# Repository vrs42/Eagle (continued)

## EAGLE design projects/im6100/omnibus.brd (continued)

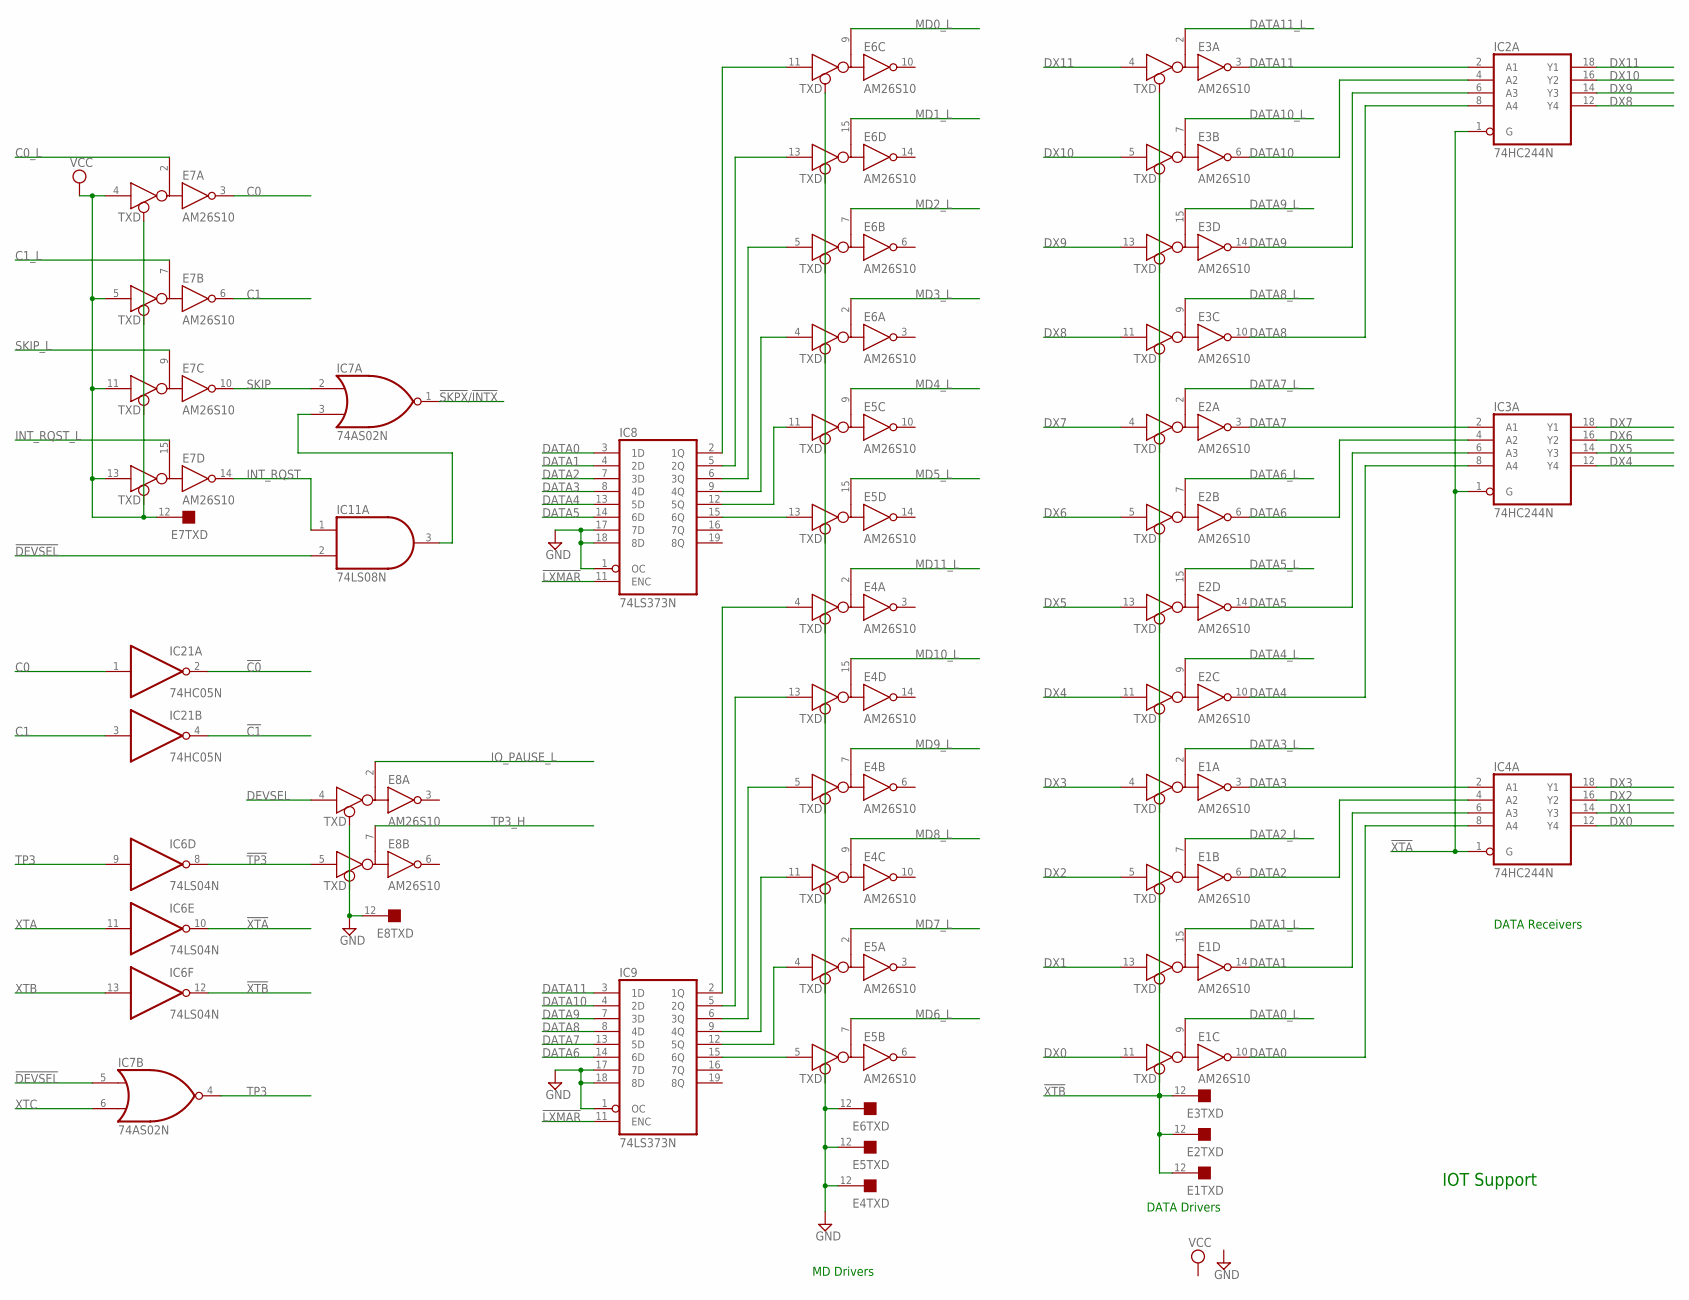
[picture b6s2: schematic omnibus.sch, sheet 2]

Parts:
E1, E2, E3, E4, E5, E6, E7, E8: AM26S10; DIL16
IC2, IC3, IC4: 74HC244N; DIL20
IC6: 74LS04N; DIL14
IC7: 74AS02N; DIL14
IC8, IC9: 74LS373N; DIL20
IC11: 74LS08N; DIL14
IC21: 74HC05N; DIL14

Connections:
!C0: IC21.2 (O); also elsewhere on the board
!C1: IC21.4 (O); also elsewhere on the board
!DEVSEL: IC7.5 (I0), IC11.2 (I1); also elsewhere on the board
!LXMAR: IC8.11 (ENC), IC9.11 (ENC)
!SKPX!/!INTX: IC7.1 (O); also elsewhere on the board
!TP3: E8.5 (D), IC6.8 (O)
!XTA: IC2.1 (G), IC3.1 (G), IC4.1 (G), IC6.10 (O)
!XTB: E1.12 (TXD), E2.12 (TXD), E3.12 (TXD), IC6.12 (O)
C0: E7.3 (R), IC21.1 (I)
C0_L: E7.2 (B); also elsewhere on the board
C1: E7.6 (R), IC21.3 (I)
C1_L: E7.7 (B); also elsewhere on the board
DATA0: E1.10 (R), IC4.8 (A4), IC8.3 (1D)
DATA0_L: E1.9 (B); also elsewhere on the board
DATA1: E1.14 (R), IC4.6 (A3), IC8.4 (2D)
DATA1_L: E1.15 (B); also elsewhere on the board
DATA2: E1.6 (R), IC4.4 (A2), IC8.7 (3D)
DATA2_L: E1.7 (B); also elsewhere on the board
DATA3: E1.3 (R), IC4.2 (A1), IC8.8 (4D)
DATA3_L: E1.2 (B); also elsewhere on the board
DATA4: E2.10 (R), IC3.8 (A4), IC8.13 (5D)
DATA4_L: E2.9 (B); also elsewhere on the board
DATA5: E2.14 (R), IC3.6 (A3), IC8.14 (6D)
DATA5_L: E2.15 (B); also elsewhere on the board
DATA6: E2.6 (R), IC3.4 (A2), IC9.14 (6D)
DATA6_L: E2.7 (B); also elsewhere on the board
DATA7: E2.3 (R), IC3.2 (A1), IC9.13 (5D)
DATA7_L: E2.2 (B); also elsewhere on the board
DATA8: E3.10 (R), IC2.8 (A4), IC9.8 (4D)
DATA8_L: E3.9 (B); also elsewhere on the board
DATA9: E3.14 (R), IC2.6 (A3), IC9.7 (3D)
DATA9_L: E3.15 (B); also elsewhere on the board
DATA10: E3.6 (R), IC2.4 (A2), IC9.4 (2D)
DATA10_L: E3.7 (B); also elsewhere on the board
DATA11: E3.3 (R), IC2.2 (A1), IC9.3 (1D)
DATA11_L: E3.2 (B); also elsewhere on the board
DEVSEL: E8.4 (D); also elsewhere on the board
DX0: E1.11 (D), IC4.12 (Y4); also elsewhere on the board
DX1: E1.13 (D), IC4.14 (Y3); also elsewhere on the board
DX2: E1.5 (D), IC4.16 (Y2); also elsewhere on the board
DX3: E1.4 (D), IC4.18 (Y1); also elsewhere on the board
DX4: E2.11 (D), IC3.12 (Y4); also elsewhere on the board
DX5: E2.13 (D), IC3.14 (Y3); also elsewhere on the board
DX6: E2.5 (D), IC3.16 (Y2); also elsewhere on the board
DX7: E2.4 (D), IC3.18 (Y1); also elsewhere on the board
DX8: E3.11 (D), IC2.12 (Y4); also elsewhere on the board
DX9: E3.13 (D), IC2.14 (Y3); also elsewhere on the board
DX10: E3.5 (D), IC2.16 (Y2); also elsewhere on the board
DX11: E3.4 (D), IC2.18 (Y1); also elsewhere on the board
GND: E1.1 (GND), E1.8 (GND), E2.1 (GND), E2.8 (GND), E3.1 (GND), E3.8 (GND), E4.1 (GND), E4.8 (GND), E4.12 (TXD), E5.1 (GND), E5.8 (GND), E5.12 (TXD), E6.1 (GND), E6.8 (GND), E6.12 (TXD), E7.1 (GND), E7.8 (GND), E8.1 (GND), E8.8 (GND), E8.12 (TXD), IC2.10 (GND), IC3.10 (GND), IC4.10 (GND), IC6.7 (GND), IC7.7 (GND), IC8.1 (OC), IC8.10 (GND), IC8.17 (7D), IC8.18 (8D), IC9.1 (OC), IC9.10 (GND), IC9.17 (7D), IC9.18 (8D), IC11.7 (GND), IC21.7 (GND); also elsewhere on the board
INT_RQST: E7.14 (R), IC11.1 (I0)
INT_RQST_L: E7.15 (B); also elsewhere on the board
IO_PAUSE_L: E8.2 (B); also elsewhere on the board
MD0_L: E6.9 (B); also elsewhere on the board
MD1_L: E6.15 (B); also elsewhere on the board
MD2_L: E6.7 (B); also elsewhere on the board
MD3_L: E6.2 (B); also elsewhere on the board
MD4_L: E5.9 (B); also elsewhere on the board
MD5_L: E5.15 (B); also elsewhere on the board
MD6_L: E5.7 (B); also elsewhere on the board
MD7_L: E5.2 (B); also elsewhere on the board
MD8_L: E4.9 (B); also elsewhere on the board
MD9_L: E4.7 (B); also elsewhere on the board
MD10_L: E4.15 (B); also elsewhere on the board
MD11_L: E4.2 (B); also elsewhere on the board
unnamed: IC7.3 (I1), IC11.3 (O)
unnamed: E6.11 (D), IC8.2 (1Q)
unnamed: E6.13 (D), IC8.5 (2Q)
unnamed: E6.5 (D), IC8.6 (3Q)
unnamed: E6.4 (D), IC8.9 (4Q)
unnamed: E5.11 (D), IC8.12 (5Q)
unnamed: E5.13 (D), IC8.15 (6Q)
unnamed: E5.5 (D), IC9.15 (6Q)
unnamed: E5.4 (D), IC9.12 (5Q)
unnamed: E4.11 (D), IC9.9 (4Q)
unnamed: E4.5 (D), IC9.6 (3Q)
unnamed: E4.13 (D), IC9.5 (2Q)
unnamed: E4.4 (D), IC9.2 (1Q)
SKIP: E7.10 (R), IC7.2 (I0)
SKIP_L: E7.9 (B); also elsewhere on the board
TP3: IC6.9 (I), IC7.4 (O)
TP3_H: E8.7 (B); also elsewhere on the board
VCC: E1.16 (VCC), E2.16 (VCC), E3.16 (VCC), E4.16 (VCC), E5.16 (VCC), E6.16 (VCC), E7.4 (D), E7.5 (D), E7.11 (D), E7.12 (TXD), E7.13 (D), E7.16 (VCC), E8.16 (VCC), IC2.20 (VCC), IC3.20 (VCC), IC4.20 (VCC), IC6.14 (VCC), IC7.14 (VCC), IC8.20 (VCC), IC9.20 (VCC), IC11.14 (VCC), IC21.14 (VCC); also elsewhere on the board
XTA: IC6.11 (I); also elsewhere on the board
XTB: IC6.13 (I); also elsewhere on the board
XTC: IC7.6 (I1); also elsewhere on the board

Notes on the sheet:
DATA Drivers
DATA Receivers
MD Drivers
IOT Support

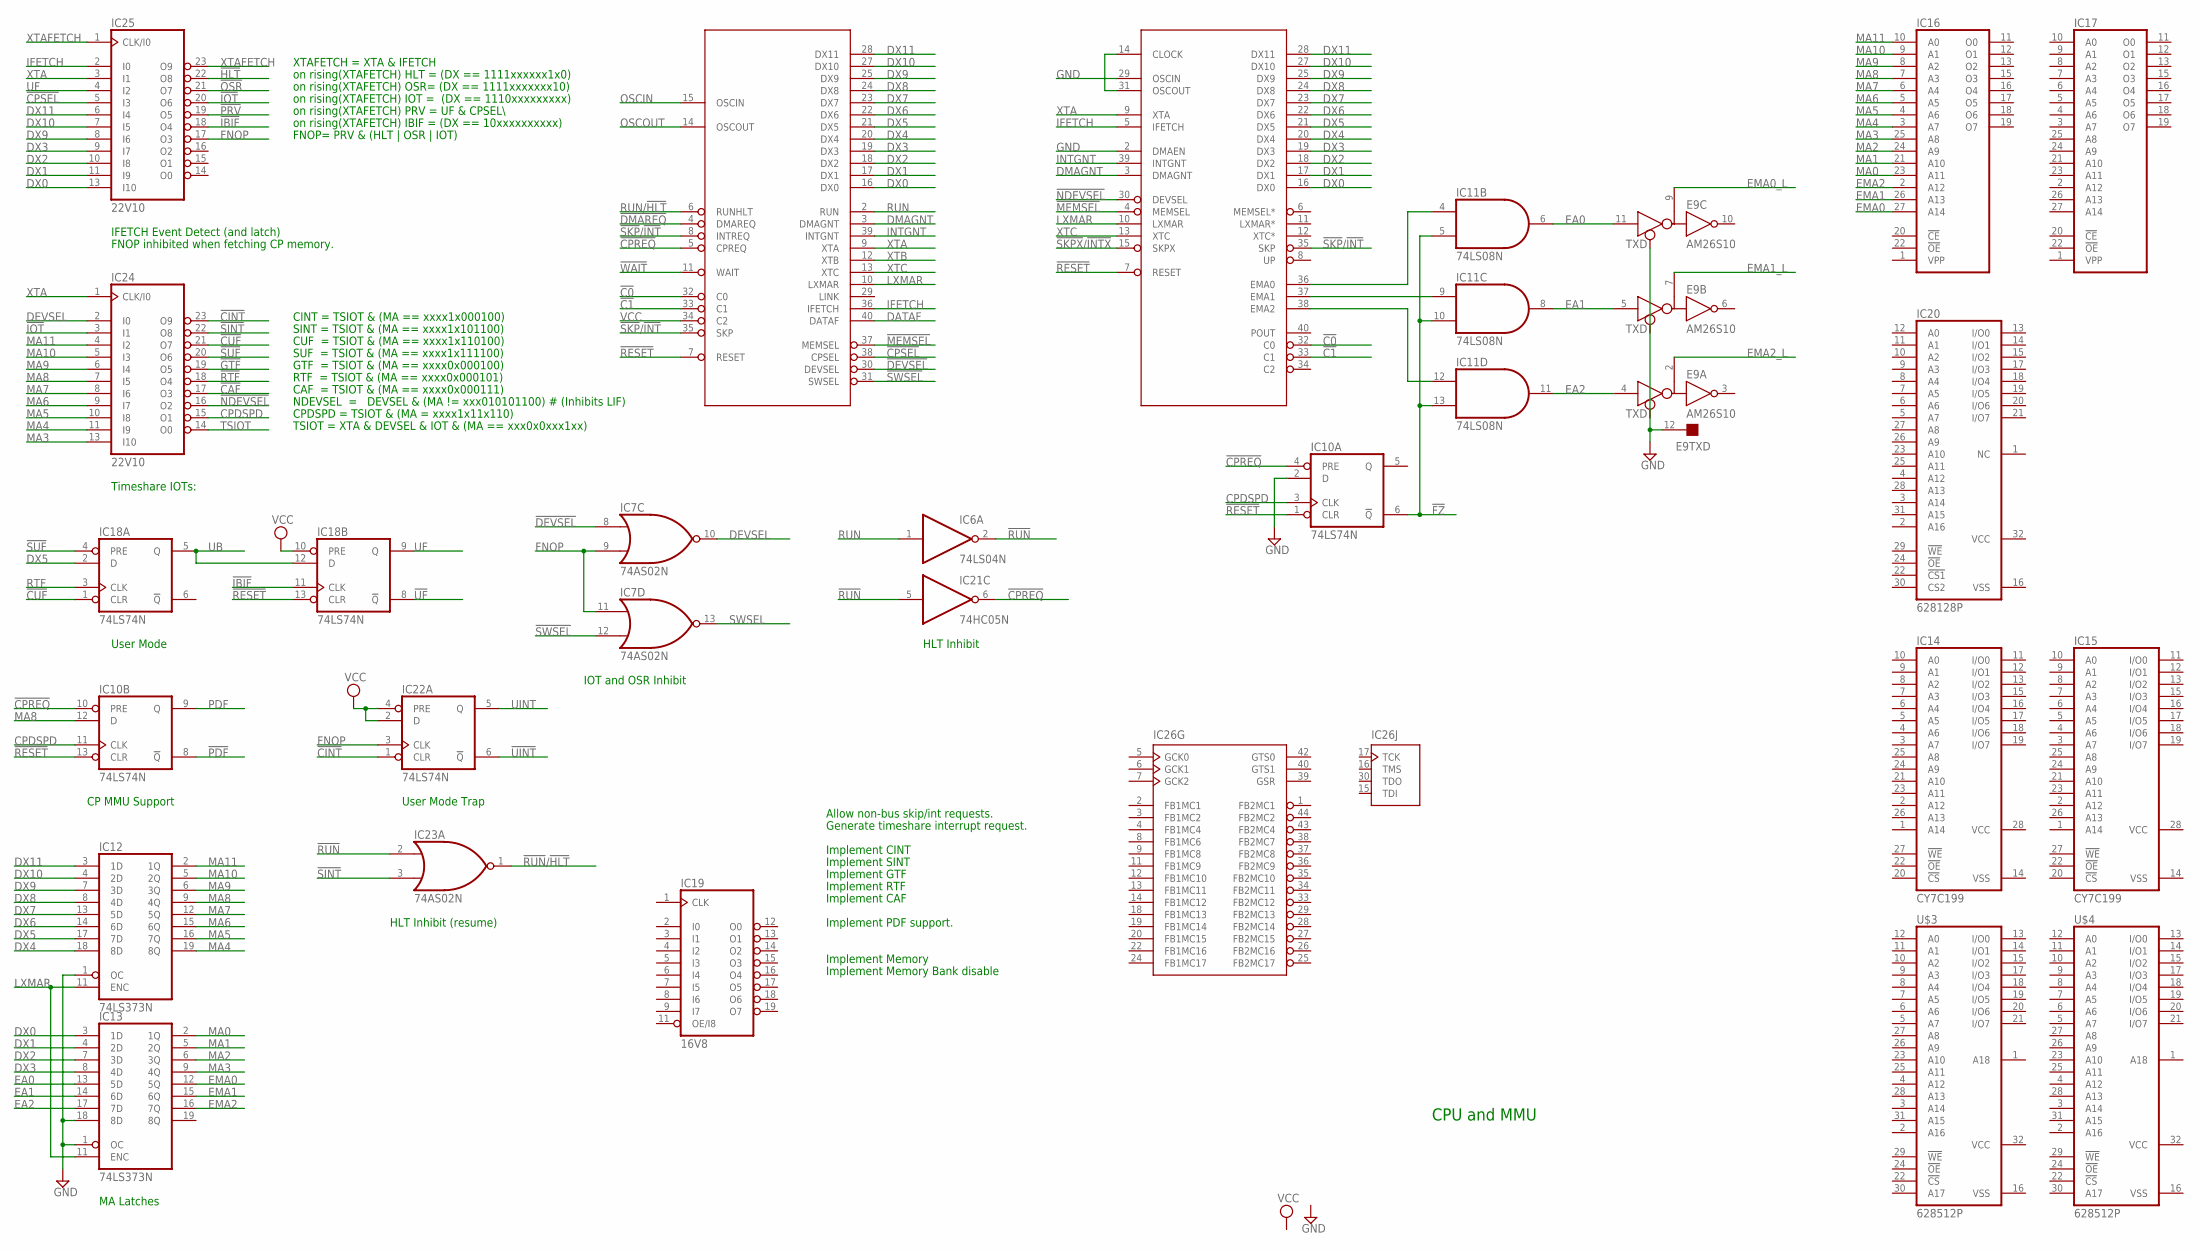
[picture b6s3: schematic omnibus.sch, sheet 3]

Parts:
E9: AM26S10; DIL16
IC1: IM6100; DIL40
IC5: IM6102; DIL40
IC6: 74LS04N; DIL14
IC7, IC23: 74AS02N; DIL14
IC10, IC18, IC22: 74LS74N; DIL14
IC11: 74LS08N; DIL14
IC12, IC13: 74LS373N; DIL20
IC14, IC15: CY7C199; DIL28-3
IC16, IC17: 27256; DIL28
IC19: 16V8; DIL20
IC20: 628128P; DIL32
IC21: 74HC05N; DIL14
IC24, IC25: 22V10; DIL24-3
IC26: XC9536-44; PLCC-S44
U$3, U$4: 628512P; DIL32

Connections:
!C0: IC1.32 (C0), IC5.32 (C0); also elsewhere on the board
!C1: IC1.33 (C1), IC5.33 (C1); also elsewhere on the board
!CAF: IC24.17 (O3)
!CINT: IC22.1 (CLR), IC24.23 (O9)
!CPREQ: IC1.5 (CPREQ), IC10.4 (PRE), IC10.10 (PRE), IC21.6 (O)
!CPSEL: IC1.38 (CPSEL), IC25.5 (I3)
!CUF: IC18.1 (CLR), IC24.21 (O7)
!DEVSEL: IC1.30 (DEVSEL), IC7.8 (I0); also elsewhere on the board
!DMAREQ: IC1.4 (DMAREQ)
!FZ: IC10.6 (!Q), IC11.5 (I1), IC11.10 (I1), IC11.13 (I1)
!GTF: IC24.19 (O5)
!HLT: IC25.22 (O8)
!IBIF: IC18.11 (CLK), IC25.18 (O4)
!IOT: IC24.3 (I1), IC25.20 (O6)
!MEMSEL: IC1.37 (MEMSEL), IC5.4 (MEMSEL)
!NDEVSEL: IC5.30 (DEVSEL), IC24.16 (O2)
!OSR: IC25.21 (O7)
!PDF: IC10.8 (!Q)
!PRV: IC25.19 (O5)
!RESET: IC1.7 (RESET), IC5.7 (RESET), IC10.1 (CLR), IC10.13 (CLR), IC18.13 (CLR)
!RTF: IC24.18 (O4)
!RUN: IC6.2 (O), IC21.5 (I), IC23.2 (I0)
!RUN!/!HLT: IC23.1 (O)
!SINT: IC23.3 (I1), IC24.22 (O8)
!SKP!/!INT: IC1.8 (INTREQ), IC1.35 (SKP), IC5.35 (SKP)
!SKPX!/!INTX: IC5.15 (SKPX); also elsewhere on the board
!SUF: IC18.4 (PRE), IC24.20 (O6)
!SWSEL: IC1.31 (SWSEL), IC7.12 (I1)
!UF: IC18.8 (!Q)
!UINT: IC22.6 (!Q)
!WAIT: IC1.11 (WAIT)
CPDSPD: IC10.3 (CLK), IC10.11 (CLK), IC24.15 (O1)
DATAF: IC1.40 (DATAF)
DEVSEL: IC7.10 (O), IC24.2 (I0); also elsewhere on the board
DMAGNT: IC1.3 (DMAGNT), IC5.3 (DMAGNT)
DX0: IC1.16 (DX0), IC5.16 (DX0), IC13.3 (1D), IC25.13 (I10); also elsewhere on the board
DX1: IC1.17 (DX1), IC5.17 (DX1), IC13.4 (2D), IC25.11 (I9); also elsewhere on the board
DX2: IC1.18 (DX2), IC5.18 (DX2), IC13.7 (3D), IC25.10 (I8); also elsewhere on the board
DX3: IC1.19 (DX3), IC5.19 (DX3), IC13.8 (4D), IC25.9 (I7); also elsewhere on the board
DX4: IC1.20 (DX4), IC5.20 (DX4), IC12.18 (8D); also elsewhere on the board
DX5: IC1.21 (DX5), IC5.21 (DX5), IC12.17 (7D), IC18.2 (D); also elsewhere on the board
DX6: IC1.22 (DX6), IC5.22 (DX6), IC12.14 (6D); also elsewhere on the board
DX7: IC1.23 (DX7), IC5.23 (DX7), IC12.13 (5D); also elsewhere on the board
DX8: IC1.24 (DX8), IC5.24 (DX8), IC12.8 (4D); also elsewhere on the board
DX9: IC1.25 (DX9), IC5.25 (DX9), IC12.7 (3D), IC25.8 (I6); also elsewhere on the board
DX10: IC1.27 (DX10), IC5.27 (DX10), IC12.4 (2D), IC25.7 (I5); also elsewhere on the board
DX11: IC1.28 (DX11), IC5.28 (DX11), IC12.3 (1D), IC25.6 (I4); also elsewhere on the board
EA0: E9.11 (D), IC11.6 (O), IC13.13 (5D)
EA1: E9.5 (D), IC11.8 (O), IC13.14 (6D)
EA2: E9.4 (D), IC11.11 (O), IC13.17 (7D)
EMA0: IC13.12 (5Q), IC16.27 (A14)
EMA0_L: E9.9 (B); also elsewhere on the board
EMA1: IC13.15 (6Q), IC16.26 (A13)
EMA1_L: E9.7 (B); also elsewhere on the board
EMA2: IC13.16 (7Q), IC16.2 (A12)
EMA2_L: E9.2 (B); also elsewhere on the board
FNOP: IC7.9 (I1), IC7.11 (I0), IC22.3 (CLK), IC25.17 (O3)
GND: E9.1 (GND), E9.8 (GND), E9.12 (TXD), IC1.26 (GND), IC5.2 (DMAEN), IC5.26 (GND), IC5.29 (OSCIN), IC6.7 (GND), IC7.7 (GND), IC10.2 (D), IC10.7 (GND), IC11.7 (GND), IC12.1 (OC), IC12.10 (GND), IC13.1 (OC), IC13.10 (GND), IC13.18 (8D), IC16.14 (GND), IC17.14 (GND), IC18.7 (GND), IC19.10 (GND), IC21.7 (GND), IC22.7 (GND), IC23.7 (GND), IC24.12 (GND), IC25.12 (GND), IC26.10 (GND), IC26.23 (GND), IC26.31 (GND); also elsewhere on the board
IFETCH: IC1.36 (IFETCH), IC5.5 (IFETCH), IC25.2 (I0)
INTGNT: IC1.39 (INTGNT), IC5.39 (INTGNT)
LXMAR: IC1.10 (LXMAR), IC5.10 (LXMAR), IC12.11 (ENC), IC13.11 (ENC)
MA0: IC13.2 (1Q), IC16.23 (A11)
MA1: IC13.5 (2Q), IC16.21 (A10)
MA2: IC13.6 (3Q), IC16.24 (A9)
MA3: IC13.9 (4Q), IC16.25 (A8), IC24.13 (I10)
MA4: IC12.19 (8Q), IC16.3 (A7), IC24.11 (I9)
MA5: IC12.16 (7Q), IC16.4 (A6), IC24.10 (I8)
MA6: IC12.15 (6Q), IC16.5 (A5), IC24.9 (I7)
MA7: IC12.12 (5Q), IC16.6 (A4), IC24.8 (I6)
MA8: IC10.12 (D), IC12.9 (4Q), IC16.7 (A3), IC24.7 (I5)
MA9: IC12.6 (3Q), IC16.8 (A2), IC24.6 (I4)
MA10: IC12.5 (2Q), IC16.9 (A1), IC24.5 (I3)
MA11: IC12.2 (1Q), IC16.10 (A0), IC24.4 (I2)
unnamed: IC5.14 (CLOCK), IC5.31 (OSCOUT)
unnamed: IC5.37 (EMA1), IC11.9 (I0)
unnamed: IC5.36 (EMA0), IC11.4 (I0)
unnamed: IC5.38 (EMA2), IC11.12 (I0)
OSCIN: IC1.15 (OSCIN)
OSCOUT: IC1.14 (OSCOUT)
PDF: IC10.9 (Q)
RTF: IC18.3 (CLK)
RUN: IC1.2 (RUN), IC6.1 (I)
RUN/!HLT: IC1.6 (RUNHLT)
SWSEL: IC7.13 (O)
TSIOT: IC24.14 (O0)
UB: IC18.5 (Q), IC18.12 (D)
UF: IC18.9 (Q), IC25.4 (I2)
UINT: IC22.5 (Q)
VCC: E9.16 (VCC), IC1.1 (VCC), IC1.34 (C2), IC5.1 (VCC), IC6.14 (VCC), IC7.14 (VCC), IC10.14 (VCC), IC11.14 (VCC), IC12.20 (VCC), IC13.20 (VCC), IC14.28 (VCC), IC15.28 (VCC), IC16.28 (VCC), IC17.28 (VCC), IC18.10 (PRE), IC18.14 (VCC), IC19.20 (VCC), IC20.32 (VCC), IC21.14 (VCC), IC22.2 (D), IC22.4 (PRE), IC22.14 (VCC), IC23.14 (VCC), IC24.24 (VCC), IC25.24 (VCC), IC26.21 (VCC), IC26.32 (VCC), IC26.41 (VCC), U$3.32 (VCC), U$4.32 (VCC); also elsewhere on the board
VSS: IC14.14 (VSS), IC15.14 (VSS), IC20.16 (VSS), U$3.16 (VSS), U$4.16 (VSS)
XTA: IC1.9 (XTA), IC5.9 (XTA), IC24.1 (CLK/I0), IC25.3 (I1); also elsewhere on the board
XTAFETCH: IC25.1 (CLK/I0), IC25.23 (O9)
XTB: IC1.12 (XTB); also elsewhere on the board
XTC: IC1.13 (XTC), IC5.13 (XTC); also elsewhere on the board

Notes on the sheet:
CPU and MMU
Timeshare IOTs:
CINT = TSIOT & (MA == xxxx1x000100)
SINT = TSIOT & (MA == xxxx1x101100)
CUF = TSIOT & (MA == xxxx1x110100)
SUF = TSIOT & (MA == xxxx1x111100)
GTF = TSIOT & (MA == xxxx0x000100)
RTF = TSIOT & (MA == xxxx0x000101)
CAF = TSIOT & (MA == xxxx0x000111)
NDEVSEL = DEVSEL & (MA \!= xxx010101100) # (Inhibits LIF)
CPDSPD = TSIOT & (MA = xxxx1x11x110)
IFETCH Event Detect (and latch)
on rising(XTAFETCH) HLT = (DX == 1111xxxxxx1x0)
on rising(XTAFETCH) OSR= (DX == 1111xxxxxxx10)
on rising(XTAFETCH) IOT = (DX == 1110xxxxxxxxx)
FNOP= PRV & (HLT | OSR | IOT)
on rising(XTAFETCH) IBIF = (DX == 10xxxxxxxxxx)
XTAFETCH = XTA & IFETCH
TSIOT = XTA & DEVSEL & IOT & (MA == xxx0x0xxx1xx)
on rising(XTAFETCH) PRV = UF & CPSEL\\
FNOP inhibited when fetching CP memory.
MA Latches
User Mode
CP MMU Support
IOT and OSR Inhibit
HLT Inhibit
Generate timeshare interrupt request.
Allow non-bus skip/int requests.
Implement CINT
Implement SINT
Implement GTF
Implement RTF
Implement CAF
Implement Memory
Implement Memory Bank disable
Implement PDF support.
HLT Inhibit (resume)
User Mode Trap

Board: 2 copper layers, 39 parts (0 on the bottom side), 138 nets, no tracks yet.

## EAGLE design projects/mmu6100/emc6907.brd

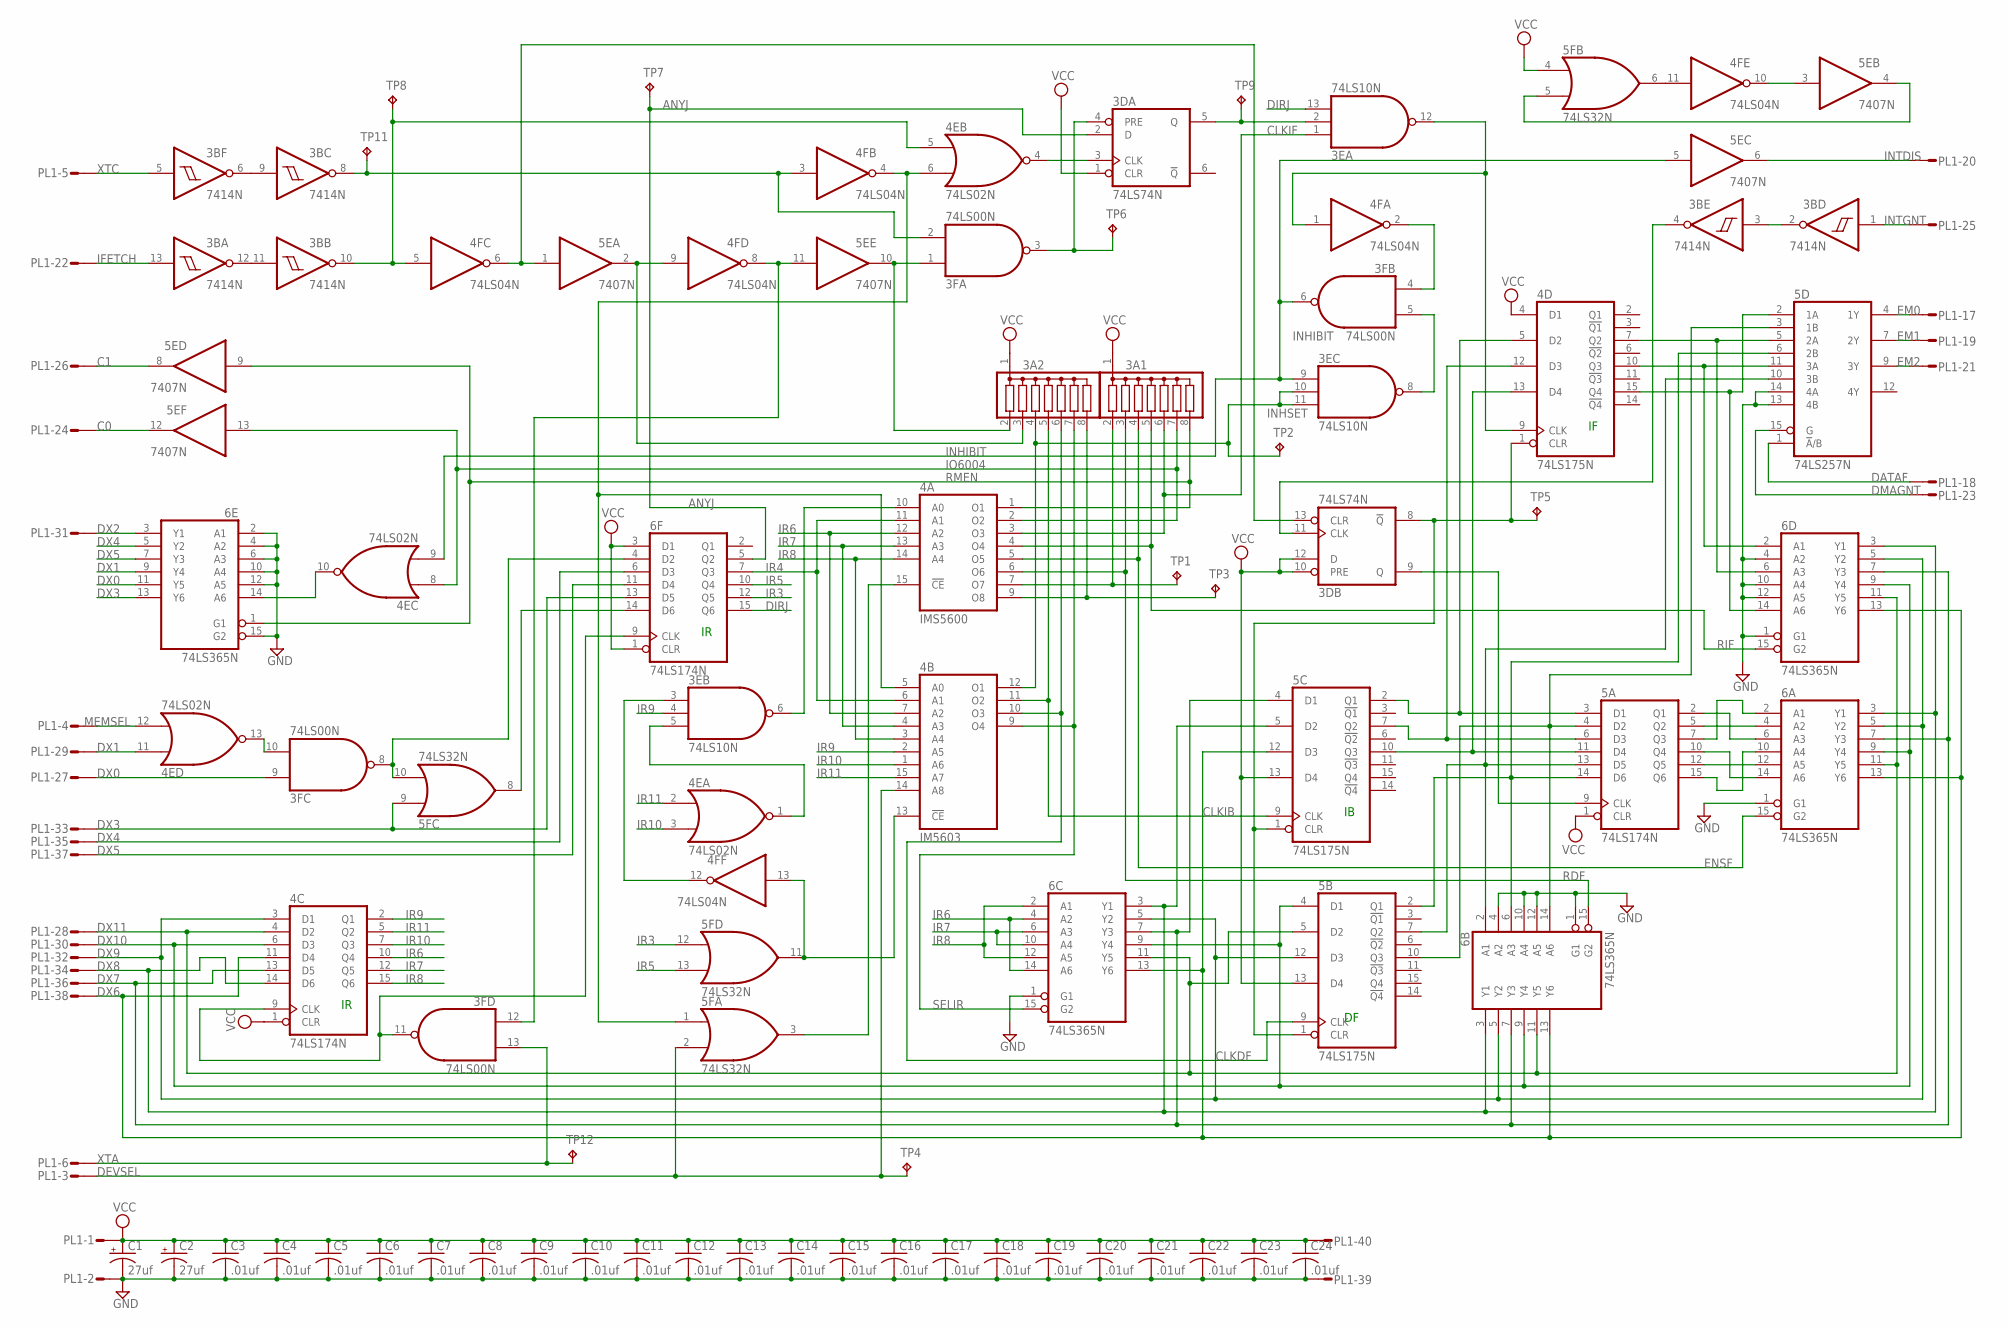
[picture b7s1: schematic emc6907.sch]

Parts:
3A1, 3A2: G07R; SIL8
3B: 7414N; DIL14
3D: 74LS74N; DIL14
3E: 74LS10N; DIL14
3F: 74LS00N; DIL14
4A: IMS5600; DIL16
4B: IM5603; DIL16
4C, 5A, 6F: 74LS174N; DIL16
4D, 5B, 5C: 74LS175N; DIL16
4E: 74LS02N; DIL14
4F: 74LS04N; DIL14
5D: 74LS257N; DIL16
5E: 7407N; DIL14
5F: 74LS32N; DIL14
6A, 6B, 6C, 6D, 6E: 74LS365N; DIL16
C1, C2: 27uf; E22-6
C3, C4, C5, C6, C7, C8, C9, C10, C11, C12, C13, C14, C15, C16, C17, C18, C19, C20, C21, C22, C23, C24: .01uf; C050-025X075
PL1: 40VS; 40V
TP1, TP2, TP3, TP4, TP5, TP6, TP7, TP8, TP9, TP11, TP12: TPPAD1-13; P1-13

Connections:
ANYJ: 3D.2 (D), 6F.5 (Q2), TP7.TP
C0: 5E.12 (O), PL1.24
C1: 5E.8 (O), PL1.26
CLKDF: 3A2.6, 4B.10 (O3), 5B.9 (CLK)
CLKIB: 3A2.5, 4B.11 (O2), 5C.9 (CLK)
CLKIF: 3A1.6, 3E.1 (I0), 4A.3 (O3)
DATAF: 5D.1 (!A!/B), PL1.18
DEVSEL: 4B.14 (A8), 5F.2 (I1), PL1.3, TP4.TP
DIRJ: 3E.13 (I2), 6F.15 (Q6)
DMAGNT: 5D.15 (G), PL1.23
DX0: 3F.9 (I0), 6E.11 (Y5), PL1.27
DX1: 4E.11 (I0), 6E.9 (Y4), PL1.29
DX2: 6E.3 (Y1), PL1.31
DX3: 5F.9 (I0), 6E.13 (Y6), 6F.13 (D5), PL1.33
DX4: 6E.5 (Y2), 6F.6 (D3), PL1.35
DX5: 6E.7 (Y3), 6F.11 (D4), PL1.37
DX6: 4C.11 (D4), 5C.12 (D3), 6A.13 (Y6), 6B.13 (Y6), 6C.13 (Y6), 6D.13 (Y6), PL1.38
DX7: 4C.13 (D5), 5C.4 (D1), 6A.7 (Y3), 6B.7 (Y3), 6C.7 (Y3), 6D.7 (Y3), PL1.36
DX8: 4C.14 (D6), 5C.5 (D2), 6A.3 (Y1), 6B.3 (Y1), 6C.3 (Y1), 6D.3 (Y1), PL1.34
DX9: 4C.3 (D1), 5B.12 (D3), 6A.5 (Y2), 6B.5 (Y2), 6C.5 (Y2), 6D.5 (Y2), PL1.32
DX10: 4C.6 (D3), 5B.4 (D1), 6A.9 (Y4), 6B.9 (Y4), 6C.9 (Y4), 6D.9 (Y4), PL1.30
DX11: 4C.4 (D2), 5B.5 (D2), 6A.11 (Y5), 6B.11 (Y5), 6C.11 (Y5), 6D.11 (Y5), PL1.28
EM0: 5D.4 (1Y), PL1.17
EM1: 5D.7 (2Y), PL1.19
EM2: 5D.9 (3Y), PL1.21
ENSF: 3A1.4, 4A.5 (O5), 6A.15 (G2)
GND: 3B.7 (GND), 3D.7 (GND), 3E.7 (GND), 3F.7 (GND), 4A.8 (GND), 4B.8 (GND), 4C.8 (GND), 4D.8 (GND), 4E.7 (GND), 4F.7 (GND), 5A.8 (GND), 5B.8 (GND), 5C.8 (GND), 5D.8 (GND), 5D.13 (4B), 5D.14 (4A), 5E.7 (GND), 5F.7 (GND), 6A.1 (G1), 6A.8 (GND), 6B.1 (G1), 6B.4 (A2), 6B.8 (GND), 6B.10 (A4), 6B.12 (A5), 6C.1 (G1), 6C.8 (GND), 6D.1 (G1), 6D.4 (A2), 6D.8 (GND), 6D.10 (A4), 6D.12 (A5), 6E.2 (A1), 6E.4 (A2), 6E.6 (A3), 6E.8 (GND), 6E.10 (A4), 6E.12 (A5), 6E.15 (G2), 6F.8 (GND), C1.-, C2.-, C3.2, C4.2, C5.2, C6.2, C7.2, C8.2, C9.2, C10.2, C11.2, C12.2, C13.2, C14.2, C15.2, C16.2, C17.2, C18.2, C19.2, C20.2, C21.2, C22.2, C23.2, C24.2, PL1.2, PL1.39
IFETCH: 3B.13 (I), PL1.22
INHIBIT: 3E.9 (I0), 3F.6 (O), 4E.9 (I1), 5E.5 (I)
INHSET: 3A2.4, 3E.10 (I1), 3E.11 (I2), 4B.12 (O1), TP2.TP
INTDIS: 5E.6 (O), PL1.20
INTGNT: 3B.1 (I), PL1.25
IO6004: 3A1.7, 4A.2 (O2), 4E.8 (I0), 5E.13 (I)
IR3: 5F.12 (I0), 6F.12 (Q5)
IR4: 4A.11 (A1), 4B.6 (A1), 6F.7 (Q3)
IR5: 5F.13 (I1), 6F.10 (Q4)
IR6: 4A.12 (A2), 4B.7 (A2), 4C.10 (Q4), 6C.4 (A2), 6C.14 (A6)
IR7: 4A.13 (A3), 4B.4 (A3), 4C.12 (Q5), 6C.6 (A3), 6C.10 (A4)
IR8: 4A.14 (A4), 4B.3 (A4), 4C.15 (Q6), 6C.2 (A1), 6C.12 (A5)
IR9: 3E.4 (I1), 4B.2 (A5), 4C.2 (Q1)
IR10: 4B.1 (A6), 4C.7 (Q3), 4E.3 (I1)
IR11: 4B.15 (A7), 4C.5 (Q2), 4E.2 (I0)
LOADIR: 3F.11 (O), 4C.9 (CLK), 6F.9 (CLK)
MEMSEL: 4E.12 (I1), PL1.4
unnamed: 3B.11 (I), 3B.12 (O)
unnamed: 3B.6 (O), 3B.9 (I)
unnamed: 3B.8 (O), 3F.2 (I1), 4F.3 (I), TP11.TP
unnamed: 3B.10 (O), 4E.5 (I0), 4F.5 (I), TP8.TP
unnamed: 3D.13 (CLR), 4F.6 (O), 5E.1 (I)
unnamed: 3D.5 (Q), 3E.2 (I1), TP9.TP
unnamed: 3A2.2, 3F.1 (I0), 5E.10 (O)
unnamed: 3F.12 (I0), 4F.8 (O), 5E.11 (I)
unnamed: 3A2.3, 4F.9 (I), 5E.2 (O)
unnamed: 4B.5 (A0), 4E.6 (I1), 4F.4 (O), 5F.1 (I0)
unnamed: 3D.3 (CLK), 4E.4 (O)
unnamed: 3D.4 (PRE), 3F.3 (O), TP6.TP
unnamed: 4F.11 (I), 5F.6 (O)
unnamed: 3F.10 (I1), 4E.13 (O)
unnamed: 4E.10 (O), 6E.14 (A6)
unnamed: 5E.4 (O), 5F.5 (I1)
unnamed: 4F.10 (O), 5E.3 (I)
unnamed: 3F.8 (O), 5F.10 (I1), 6F.4 (D2)
unnamed: 5F.8 (O), 6F.14 (D6)
unnamed: 4B.13 (!CE), 4F.13 (I), 5F.11 (O)
unnamed: 3A1.2, 4A.7 (O7), TP1.TP
unnamed: 3A2.8, 4A.9 (O8), TP3.TP
unnamed: 3E.3 (I0), 4F.12 (O)
unnamed: 3E.6 (O), 4A.10 (A0)
unnamed: 4A.15 (!CE), 5F.3 (O)
unnamed: 5A.2 (Q1), 6A.6 (A3)
unnamed: 3E.5 (I2), 4E.1 (O)
unnamed: 5A.10 (Q4), 6A.14 (A6)
unnamed: 5A.7 (Q3), 6A.2 (A1)
unnamed: 5A.5 (Q2), 6A.4 (A2)
unnamed: 5A.15 (Q6), 6A.10 (A4)
unnamed: 5A.12 (Q5), 6A.12 (A5)
unnamed: 4D.15 (Q4), 5D.2 (1A), 6D.14 (A6)
unnamed: 4D.10 (Q3), 5D.11 (3A), 6D.2 (A1)
unnamed: 4D.7 (Q2), 5D.5 (2A), 6D.6 (A3)
unnamed: 3D.8 (!Q), 4D.1 (CLR), 5B.1 (CLR), 5C.1 (CLR), TP5.TP
unnamed: 4D.13 (D4), 5A.11 (D4), 5C.10 (Q3)
unnamed: 4D.5 (D2), 5A.3 (D1), 5C.2 (Q1)
unnamed: 4D.12 (D3), 5A.6 (D3), 5C.7 (Q2)
unnamed: 5A.4 (D2), 5B.10 (Q3), 5D.3 (1B), 6B.14 (A6)
unnamed: 5A.14 (D6), 5B.2 (Q1), 5D.6 (2B), 6B.6 (A3)
unnamed: 5A.13 (D5), 5B.7 (Q2), 5D.10 (3B), 6B.2 (A1)
unnamed: 3D.9 (Q), 5A.9 (CLK)
unnamed: 3E.12 (O), 4D.9 (CLK), 4F.1 (I)
unnamed: 3E.8 (O), 3F.5 (I1)
unnamed: 3F.4 (I0), 4F.2 (O)
unnamed: 3B.2 (O), 3B.3 (I)
unnamed: 3B.4 (O), 3D.11 (CLK)
RDF: 3A1.3, 4A.6 (O6), 6B.15 (G2)
RIF: 3A1.5, 4A.4 (O4), 6D.15 (G2)
RMEN: 3A1.8, 4A.1 (O1), 5E.9 (I), 6E.1 (G1)
SELIR: 3A2.7, 4B.9 (O4), 6C.15 (G2)
VCC: 3A1.1, 3A2.1, 3B.14 (VCC), 3D.1 (CLR), 3D.10 (PRE), 3D.12 (D), 3D.14 (VCC), 3E.14 (VCC), 3F.14 (VCC), 4A.16 (VCC), 4B.16 (VCC), 4C.1 (CLR), 4C.16 (VCC), 4D.4 (D1), 4D.16 (VCC), 4E.14 (VCC), 4F.14 (VCC), 5A.1 (CLR), 5A.16 (VCC), 5B.13 (D4), 5B.16 (VCC), 5C.13 (D4), 5C.16 (VCC), 5D.16 (VCC), 5E.14 (VCC), 5F.4 (I0), 5F.14 (VCC), 6A.16 (VCC), 6B.16 (VCC), 6C.16 (VCC), 6D.16 (VCC), 6E.16 (VCC), 6F.1 (CLR), 6F.3 (D1), 6F.16 (VCC), C1.+, C2.+, C3.1, C4.1, C5.1, C6.1, C7.1, C8.1, C9.1, C10.1, C11.1, C12.1, C13.1, C14.1, C15.1, C16.1, C17.1, C18.1, C19.1, C20.1, C21.1, C22.1, C23.1, C24.1, PL1.1, PL1.40
XTA: 3F.13 (I1), PL1.6, TP12.TP
XTC: 3B.5 (I), PL1.5

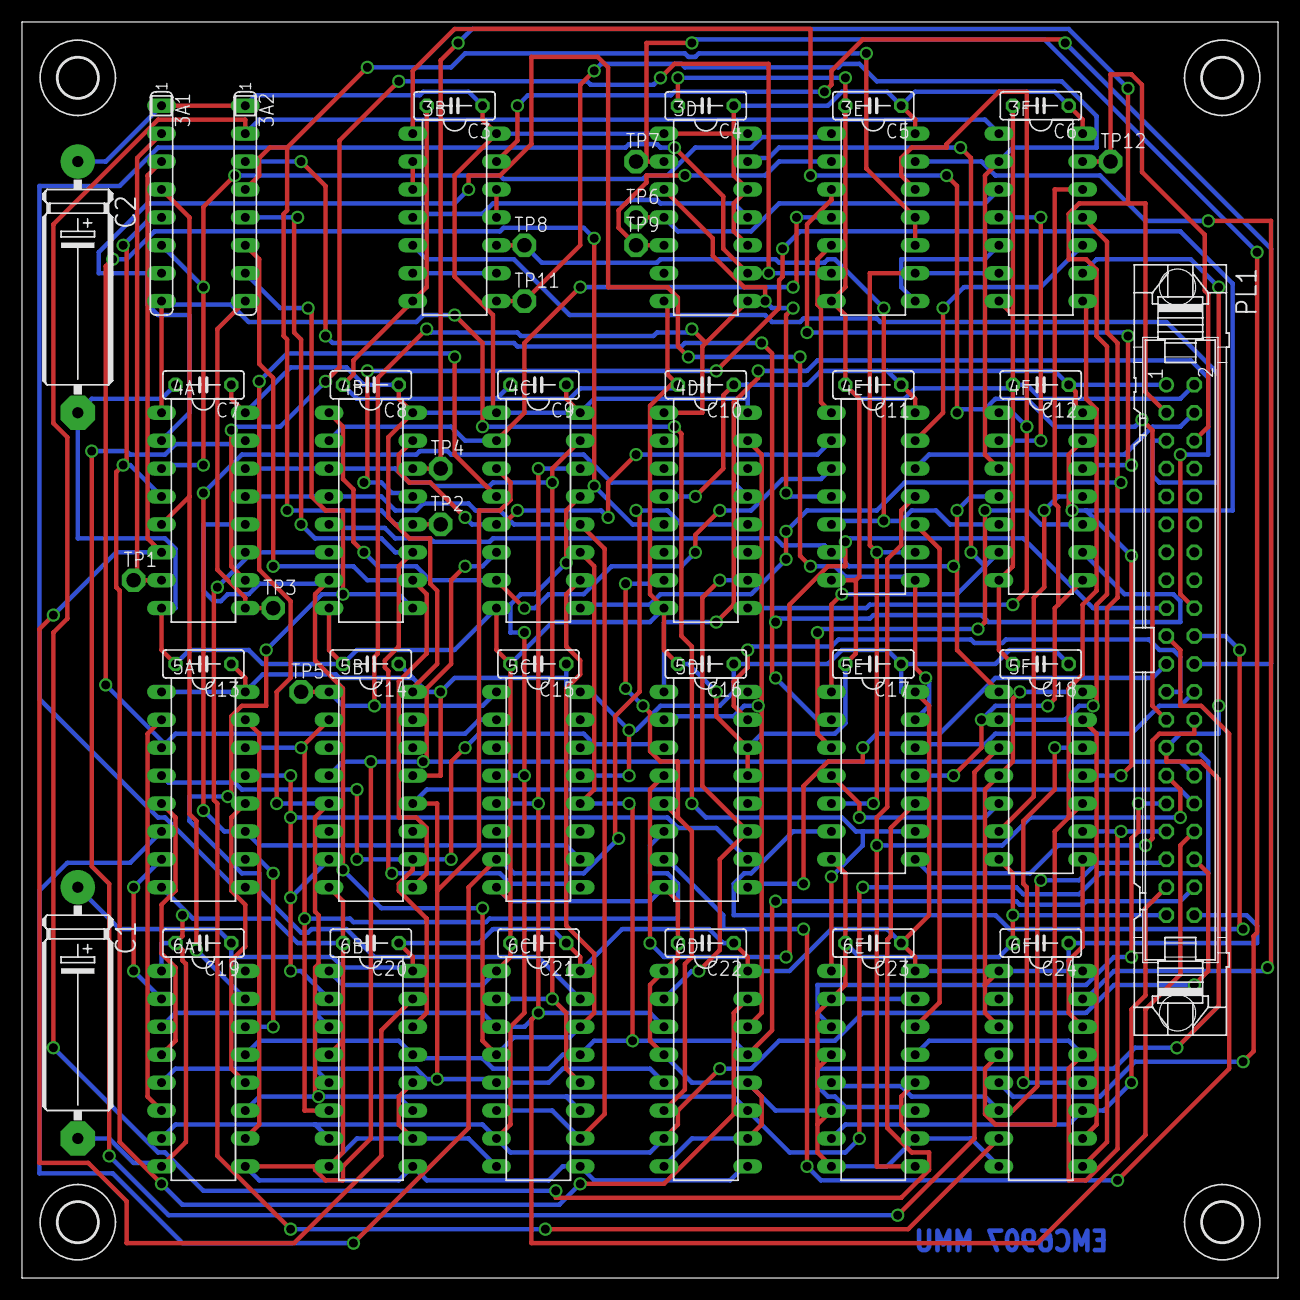
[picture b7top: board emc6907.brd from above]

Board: 2 copper layers, 114.3 x 114.3 mm, 64 parts (0 on the bottom side), 99 nets.

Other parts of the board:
U$1, U$2, U$3, U$4: 3,6
